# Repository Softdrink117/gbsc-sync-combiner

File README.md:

# GBSC Sync Combiner
V1.3  
Design by Tobias Heinemann / Softdrink 117 c. Jan 2022

-----

*A photo of an assembled GBSC Sync Combiner v1.3 PCB*

*A photo of a Sync Combiner connected to a GBS-Control setup.*

## Contents

- [Overview](#Overview)
- [Circuit Design](#Circuit-Design)
- [Board Design](#Board-Design)
- [Assembly](#Assembly)
- [BOM](#BOM)
  - [Required Components](#Required-Components)
  - [Headers](#Headers)
  - [Cable Assemblies](Cable-Assemblies)
- [Miscellaneous Notes](#Miscellaneous-Notes)
- [Acknowledgements](#Acknowledgements)

## Overview

 A simple sync combiner designed to convert RGBHV (VGA) into RGBS. Specifically built to be used with the GBS-Control project, which has some notable issues with RGBHV input under some circumstances (downscaling, etc.).

 The circuit is straightforward, using only a single logic IC and three resistors. The headers (`J2` and `J3`) are actually optional, and only included so that the module is plug-and-play compatible with the existing headers on the GBS board (`P9` and `P11`, respectively). If you wish, you can omit installation of the headers and solder wires directly between the Sync Combiner board and the GBS mainboard.

### Circuit Design

The sync combiner circuit used in this project is adapted from [TD-IO](https://github.com/tdaede/td-io), and is probably found in numerous other projects as well. It's a simplified XNOR design based around the 74x86 logic IC. Compared to other simple methods for sync combination, this is generally a very solid approach; however, it does have some limitations, and I cannot guarantee it will work with all signals.

For a more in-depth explanation of this circuit, [there's a great blog post from HD Retrovision](https://www.hdretrovision.com/blog/2019/10/10/engineering-csync-part-2-falling-short) that explains the XNOR technique in the context of other sync processing designs.

### Board Design

*Exported diagram from KiCAD's PCB editor, showing board dimensions and layout.*

The board is designed to be extremely simple. It is capable of being fabricated with a single-sided process, and measures 47mm x 33mm, with M3 mounting holes in a 25mm x 39mm pattern.

 > **Note:** There is a small solder jumper preconfigured in the closed position that links the shield of the VGA connector to ground. In the overwhelming majority of cases, this should be fine to keep closed; however, in some situations coupling the shield to ground can cause issues with interference. If you experience issues, you can cut the jumper open if necessary.

### Assembly

Due to the simple design of the circuit, basic through-hole soldering is all that is required. I'd recommend working from smaller to larger components (resistors and capacitor first, then IC and headers, and VGA connector last).

When building the (optional) cable assemblies, please take note that only six pins of the 8-pin video cable are actually used.

| 1&nbsp;&nbsp;&nbsp;&nbsp;&nbsp;&nbsp;&nbsp; | 2&nbsp;&nbsp;&nbsp;&nbsp;&nbsp;&nbsp;&nbsp; | 3&nbsp;&nbsp;&nbsp;&nbsp;&nbsp;&nbsp;&nbsp; | 4&nbsp;&nbsp;&nbsp;&nbsp;&nbsp;&nbsp;&nbsp; | 5&nbsp;&nbsp;&nbsp;&nbsp;&nbsp;&nbsp;&nbsp; | 6&nbsp;&nbsp;&nbsp;&nbsp;&nbsp;&nbsp;&nbsp; | 7&nbsp;&nbsp;&nbsp;&nbsp;&nbsp;&nbsp;&nbsp; | 8&nbsp;&nbsp;&nbsp;&nbsp;&nbsp;&nbsp;&nbsp; |
| :-: | :-: | :-: | :-: | :-: | :-: | :-: | :-: |
| Red | Green | Blue | Sync | | | GND | GND |

Also, please verify that the `P9` header on the GBS mainboard correctly indicates the power lines; the Sync Combiner will not function correctly if 5V and GND are reversed. This could result in damage to the Sync Combiner, the GBS mainboard, or even connected equipment in the worst case. I have not yet encounted a GBS board that is marked incorrectly, but there are many variations, and I cannot guarantee that all of them will match.

#### Assembly Photos

*Components for a Sync Combiner board.*

*First step of assembly: resistors and decoupling capacitor.*

*Second step of assembly: IC and headers.*

*Final step of assembly: VGA connector. Note that there is flux residue visible in this picture, which must be cleaned before use.*

### BOM

#### Required Components
| Part | Name | Quantity | Link | Notes |
| ---: | :--: | :------: | :----------- | :---- |
| J1 | Right-Angle Female VGA Connector | 1 | [Digikey](https://www.digikey.com/en/products/detail/adam-tech/HD15-SN-25/9832737) | Critical dimension is 'backset spacing' at 0.121" / 3.08mm. Many other right-angle VGA connectors exist that would be compatible.
| U1 | 74LS86 IC | 1 | [Digikey](https://www.digikey.com/en/products/detail/texas-instruments/SN74LS86AN/277315) |
| R1, R2 | 10 kOhm Resistor | 2 | [Digikey](https://www.digikey.com/en/products/detail/vishay-beyschlag-draloric-bc-components/SFR2500001002FR500/595641) | Pretty much any 10k through-hole resistor will work.
| R3 | 470 Ohm Resistor | 1 | [Digikey](https://www.digikey.com/en/products/detail/vishay-beyschlag-draloric-bc-components/SFR2500004700FR500/333902) | As above, pretty much any 470Ohm through-hole resistor will work.
| C1 | 0.1uF Capacitor | 1 | [Digikey](https://www.digikey.com/en/products/detail/vishay-beyschlag-draloric-bc-components/K104K15X7RF5TL2/286538) | Pretty much any 0.1uF decoupling capacitor with 2.5mm through-hole leads will work.

#### Headers
Optional, but allows the sync combiner to work as a plug-and-play add-on with corresponding cables. Omitting the headers will require directly soldering wires between the Sync Combiner and the GBS-C mainboard.

| Part | Name | Quantity | Link | Notes |
| ---: | :--: | :------: | :----------- | :---- |
| J3 | JST B8B-XH-A | 1 | [Digikey](https://www.digikey.com/en/products/detail/jst-sales-america-inc/B8B-XH-A-LF-SN/1651049), [GAM-GEC](https://gam-gec.com/product/b8b-xh-a/) | Digikey often has low stock of JST components; GAM-GEC is a US division of JST and usually has good stock.
| J2 | JST B2B-XH-A | 1 | [Digikey](https://www.digikey.com/en/products/detail/jst-sales-america-inc/B2B-XH-A-LF-SN/1651045), [GAM-GEC](https://gam-gec.com/product/b2b-xh-a/) | As above.

#### Cable Assemblies
Cable assemblies designed to connect the Sync Combiner with the GBS-C mainboard. These specific parts will give you an 8" (200mm) cable for power, and a 4" (100mm) cable for video signals. Depending on your desired install location, you may want to choose a different cable length; [there are several options available in 2" increments between 2 and 12 inches](https://www.digikey.com/en/product-highlight/j/jst/xh-series-connectors). It is also possible to crimp your own cable assemblies.

| Part | Quantity | Link | Notes |
| ---: | :------: | :----------- | :---- |
| JST XHP-8 | 2 | [Digikey](https://www.digikey.com/en/products/detail/jst-sales-america-inc/XHP-8/923773), [GAM-GEC](https://gam-gec.com/product/xhp-8/) | Digikey often has low stock of JST components; GAM-GEC is a US division of JST and usually has good stock.
| JST XHP-2 | 2 | [Digikey](https://www.digikey.com/en/products/detail/jst-sales-america-inc/XHP-2/555485), [GAM-GEC](https://gam-gec.com/product/xhp-2/) | As above.
| JST JUMPER SXH-001T-P0.6 X2 8" | 2 | [Digikey](https://www.digikey.com/en/products/detail/jst-sales-america-inc/ASXHSXH22K203/9961918) | Digikey often has good stock of these pre-terminated XH jumper wire assemblies.
| JST JUMPER SXH-001T-P0.6 X2 4" | 6 | [Digikey](https://www.digikey.com/en/products/detail/jst-sales-america-inc/ASXHSXH22K102/9961917) | As above.

#### Miscellaneous Notes
The *output side* RGB header - P12 on the single-output boards - uses JST PHR-12 (2mm pitch). The other headers on the board are mostly JST XH.

-----

### Acknowledgements

This project would not have been possible without the help of the following people:

- ["Hatsune" Mike](https://github.com/Mikejmoffitt)
- [Thomas Daede](https://github.com/tdaede)

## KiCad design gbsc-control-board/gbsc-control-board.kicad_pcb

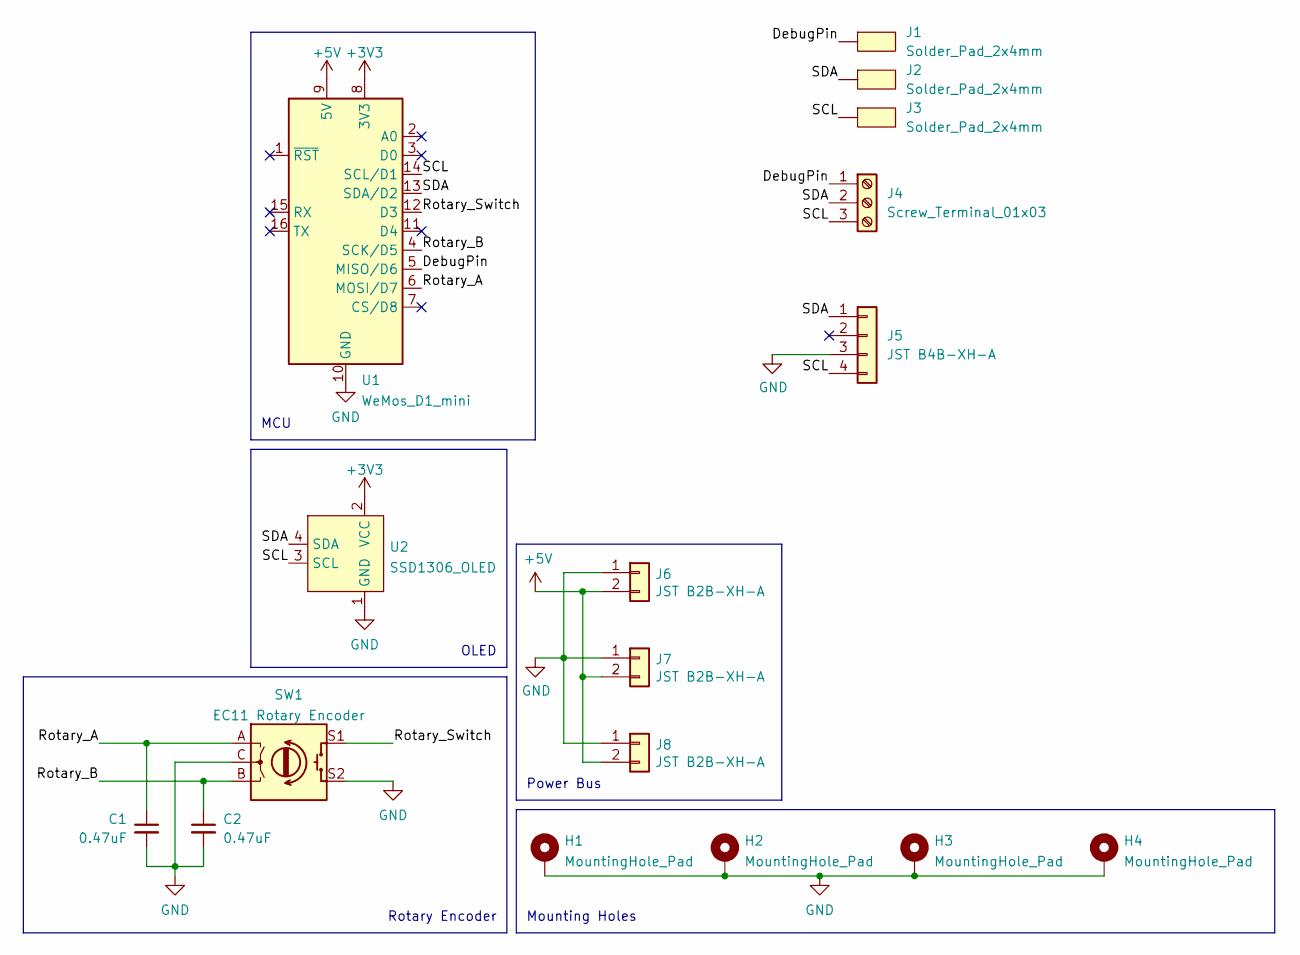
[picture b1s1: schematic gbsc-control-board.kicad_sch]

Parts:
C1, C2: 0.47uF; C_Disc_D3.0mm_W1.6mm_P2.50mm
H1, H2, H3, H4: MountingHole_Pad; MountingHole_3.2mm_M3_Pad
J1, J2, J3: Solder_Pad_2x4mm
J4: Screw_Terminal_01x03; TerminalBlock_MetzConnect_Type059_RT06303HBWC_1x03_P3.50mm_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
J5: JST B4B-XH-A; JST_XH_B4B-XH-A_1x04_P2.50mm_Vertical
J6, J7, J8: JST B2B-XH-A; JST_XH_B2B-XH-A_1x02_P2.50mm_Vertical
SW1: EC11 Rotary Encoder; RotaryEncoder_Alps_EC11E-Switch_Vertical_H20mm
U1: WeMos_D1_mini; WEMOS_D1_mini_light
U2: SSD1306_OLED; SSD1306_OLED_0.96-Inch

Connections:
+3V3: U1.8 (3V3), U2.2 (VCC)
+5V: J6.2, J7.2, J8.2, U1.9 (5V)
/DebugPin: J1.1, J4.1, U1.5 (MISO/D6)
/Rotary_A: C1.1, SW1.A, U1.6 (MOSI/D7)
/Rotary_B: C2.1, SW1.B, U1.4 (SCK/D5)
/Rotary_Switch: SW1.S1, U1.12 (D3)
/SCL: J3.1, J4.3, J5.4, U1.14 (SCL/D1), U2.3 (SCL)
/SDA: J2.1, J4.2, J5.1, U1.13 (SDA/D2), U2.4 (SDA)
GND: C1.2, C2.2, H1.1, H2.1, H3.1, H4.1, J5.3, J6.1, J7.1, J8.1, SW1.C, SW1.S2, U1.10 (GND), U2.1 (GND)

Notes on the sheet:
Mounting Holes
Rotary Encoder
Power Bus
OLED
MCU

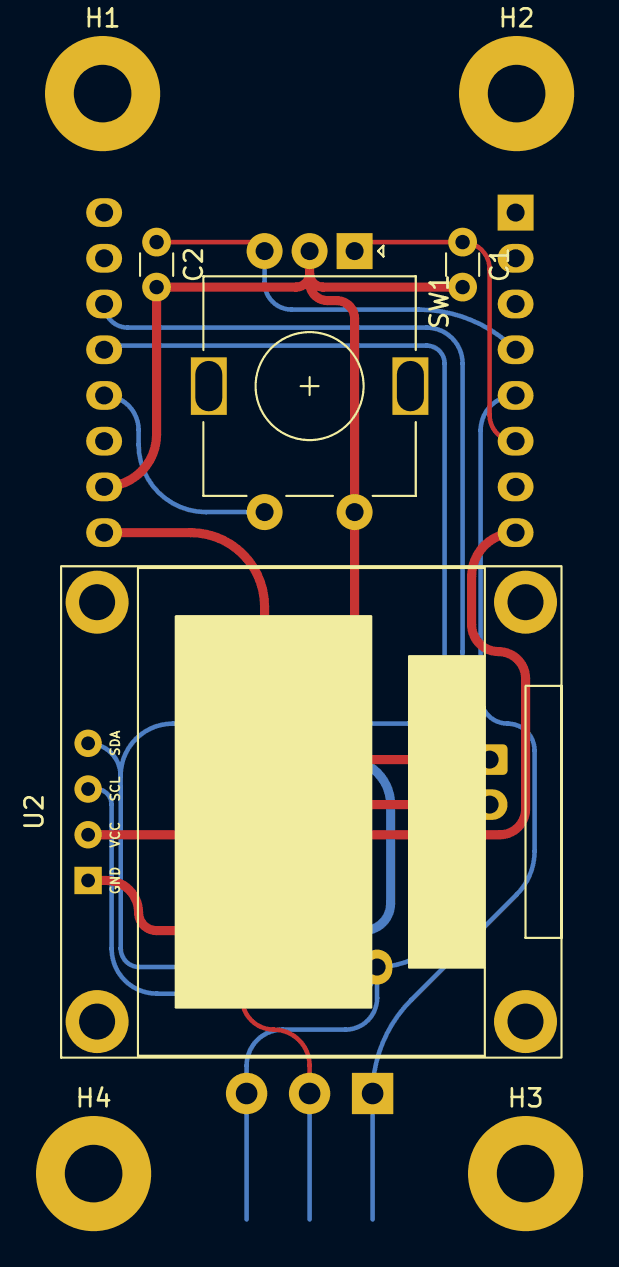
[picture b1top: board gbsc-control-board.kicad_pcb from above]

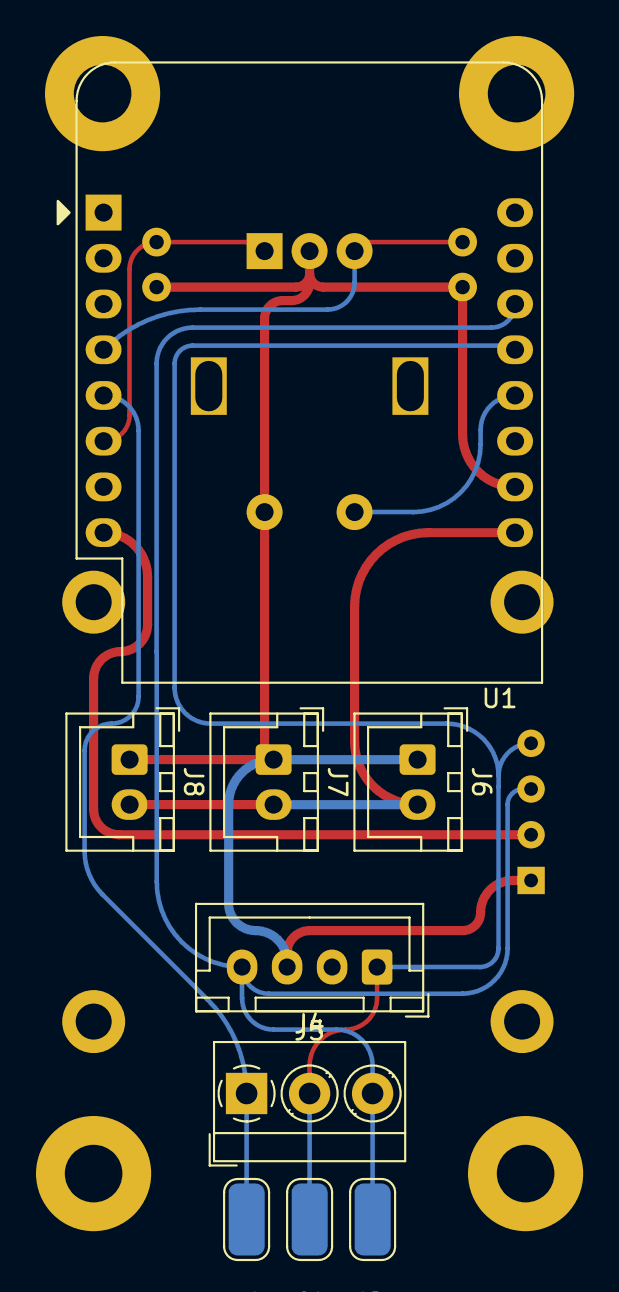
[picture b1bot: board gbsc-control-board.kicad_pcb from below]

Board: 2 copper layers, 17 parts (9 on the bottom side), 9 nets.

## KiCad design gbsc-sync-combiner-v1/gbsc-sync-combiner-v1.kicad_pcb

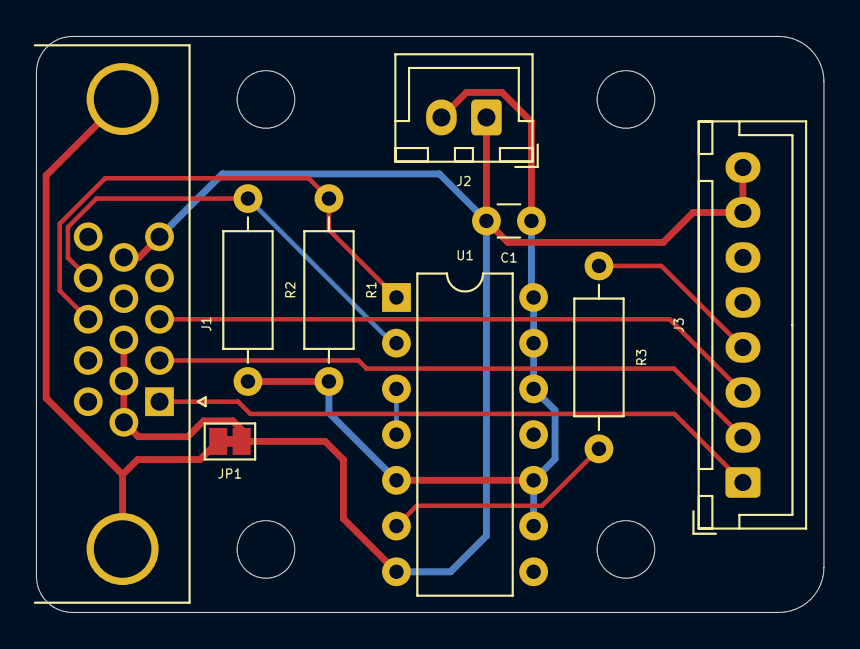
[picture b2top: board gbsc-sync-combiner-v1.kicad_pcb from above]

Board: 2 copper layers, 43.8 x 32.0 mm, 13 parts (0 on the bottom side), 11 nets.

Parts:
C1: 0.1uF; C_Disc_D3.0mm_W1.6mm_P2.50mm
H1, H2, H3, H4: MountingHole; MountingHole_3.2mm_M3
J1: DB15_Female_HighDensity_MountingHoles; DSUB-15-HD_Female_Horizontal_P2.29x1.98mm_EdgePinOffset3.03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
J2: JST-XH; JST_XH_B2B-XH-A_1x02_P2.50mm_Vertical
J3: JST-XH; JST_XH_B8B-XH-A_1x08_P2.50mm_Vertical
JP1: SolderJumper_2_Bridged; SolderJumper-2_P1.3mm_Bridged_Pad1.0x1.5mm
R1, R2: 10k; R_Axial_DIN0207_L6.3mm_D2.5mm_P10.16mm_Horizontal
R3: 470Ohm; R_Axial_DIN0207_L6.3mm_D2.5mm_P10.16mm_Horizontal
U1: 74LS86; DIP-14_W7.62mm

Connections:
+5V: C1.1, J2.2, R1.2, R2.2, U1.5, U1.9, U1.10, U1.12, U1.13, U1.14
/CSync: R3.2, U1.6
/HSync: J1.13, R1.1, U1.1
/VSync: J1.14, R2.1, U1.2
Blue: J1.3, J3.3
GND: C1.2, J1.5, J1.6, J1.7, J1.8, J1.10, J2.1, J3.7, J3.8, JP1.1, U1.7
Green: J1.2, J3.2
unnamed: J1.0, JP1.2
unnamed: J3.4, R3.1
unnamed: U1.3, U1.4
Red: J1.1, J3.1

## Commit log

2021-10-29 Initial design. Schematic and basic layout pass
2021-10-29 Added mounting holes
2021-11-01 Updated connector pinouts to match GBS board
2021-11-05 Changed existing to -v1 variant, routed board
2021-11-06 Design and route V2 board
2021-11-06 Update info-cache
2021-11-10 Adjust silks
2021-11-20 Minor adjustments
2021-11-28 Minor tweaks
2022-01-19 Created V3, updated project to Kicad 6
2022-01-19 minor adjustment
2022-01-21 Edited gitignore, minor board adjustments
2022-01-24 Major updates
    - Updated v1.3 PCB design
    - Created README
    - Created BOM
    - Created gerbers
    - Sent gerbers to fab
2022-01-27 Added a note about the output connector
2022-04-05 Created Control Board schematic, symbol library, custom symbols
2022-04-08 Created Footprint for SSD1306 OLED module
2022-05-28 Layout and route control board
2022-05-28 Vertical mounted layout nearly done
2022-06-19 Reorganize repo, move control board to another project
2022-06-19 Update README, add images and photos
2022-06-19 Update ToC
2022-06-19 Add acknowledgements
2022-09-03 Create instructions
2022-09-06 Minor updates to readme
